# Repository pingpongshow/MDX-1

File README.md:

# MDX-1

**An open, simultaneous multi-frequency + pulse-induction metal detector — hardware, search coil and firmware.**

MDX-1 is a from-scratch detector design: a KiCad schematic and 4-layer main board, a 2-layer user-interface board, a hand-wound search coil, portable C firmware with a host simulator and test bench, and iOS/Android companion apps. The receive and transmit engine is specified around a coherent, DSP-first architecture:

- **Five simultaneous VLF frequencies** — 5.12, 10.24, 15.36, 20.48 and 40.96 kHz (harmonics 1, 2, 3, 4, 8 of a 5.12 kHz fundamental) from a single optimised 3-level look-up-table waveform, so every line falls exactly on a DFT bin and demodulates with one coherent transform.
- **Two 24-bit, 512 kSPS converters** — one digitises the receive coil, the second digitises the transmit current for exact V<sub>RX</sub>/I<sub>TX</sub> normalisation. Fixed gain, no AGC or blanking.
- **A 100 V bipolar pulse-induction mode** on the same H-bridge, plus a hybrid mode that time-interleaves PI bursts between VLF periods.
- **STM32H743** (Cortex-M7, 480 MHz) with single-crystal-coherent timing, a Bluetooth audio module, a Sharp memory LCD, GNSS find-logging and an IMU for swing-aware ground tracking.

> ### Status: experimental, design stage
> This is a **paper design that has not been built or field-tested.** The schematic is ERC-checked, the PCBs are placed and routed, the firmware core passes its host test bench, and the STM32 target layer is written against the CubeH7 HAL but has not run on hardware. Nothing here has been fabricated, assembled or measured. Component values, footprints and firmware behaviour may be wrong. **Verify everything against the primary datasheets before ordering or building.**
>
> The transmit stage switches up to **100 V** through an H-bridge into an inductive load. Treat it as a hazardous-voltage circuit: it can injure you and destroy parts if mis-built. Build and power it only if you are competent with high-voltage switching electronics.

*Main board, populated (3D view). Per-layer plots for both boards are in [`hardware/mdx1/images/`](hardware/mdx1/images/).*

## Layout

| Path | What |
|---|---|
| `hardware/mdx1/mdx1.kicad_pro` | KiCad project. Open this. |
| `hardware/mdx1/*.kicad_sch` | Root sheet + hierarchical sheets (power, tx_driver, rx_frontend, adc, mcu, ui_audio_rf, coil). |
| `hardware/mdx1/mdx1.kicad_pcb` | 135 × 92 mm 4-layer main board — footprints, nets, pours, routing, outline. |
| `hardware/mdx1/mdx1_ui.kicad_pcb` | 82 × 60 mm 2-layer UI board (LCD, keypad, pinpoint trigger, power key, LEDs, front-light). |
| `hardware/mdx1/MDX*.kicad_sym`, `MDX.pretty/` | Project-local symbol/footprint libraries. |
| `hardware/mdx1/fab/` | Fabrication packages: Gerbers, drill, assembly BOM and pick-and-place for both boards (`Gerbers/`, `BOM/`, `PNP/`); interconnect BOM; enclosure DXFs (`Case/`). |
| `hardware/mdx1/images/` | Rendered board views: per-layer plots (copper, silkscreen) and a 3D top view of each board. |
| `firmware/` | Portable core (`core/`), host physics simulator + test bench (`sim/`), STM32H743 target layer (`stm32/`). `make test` runs the bench. |
| `app/ios/` | SwiftUI companion app (BLE): live status, on-detector menu, finds map, diagnostics; built-in demo detector. |
| `app/android/` | Kotlin/Compose port of the companion app. |
| `docs/MDX-1_design_report.html` | Hardware design report. |
| `docs/MDX-1_coil_manual.html` | Search-coil build manual and off-the-shelf coil path. |
| `docs/MDX-1_firmware_guide.html` | Firmware guide with test evidence and screen renders. |
| `docs/MDX-1_assembly.md` | Board population guide (build order, critical parts, mounting). |
| `docs/MDX-1_bringup.md` | Staged first-power procedure — populate/verify one subsystem at a time. |
| `docs/MDX-1_link_protocol.md` | Phone-link protocol (frames, item table, status packet, actions). |
| `docs/MDX-1_schematic.pdf` | All schematic sheets. |
| `docs/datasheets/` | Third-party component datasheets used during the design review — **not included in this repository** (vendor copyright); part numbers are in the BOM under `hardware/mdx1/fab/`. |
| `tools/` | Design toolchain — see below. |

## The toolchain

**The KiCad schematic and boards are the source of truth — they are hand-placed and hand-routed.** The remaining tools are read-only against the boards or operate on design inputs; none of them modify the `.kicad_pcb` / `.kicad_sch` files. (The original placement/schematic generators were removed to prevent accidental overwrites of the finished layout.)

| Tool | Purpose |
|---|---|
| `tools/fab_jlc.py` | Reads the boards and writes the JLCPCB fabrication package: Gerbers + drill, assembly BOM and CPL for both boards. Does not modify the boards. |
| `tools/bom_data.json` | Maintained part database (manufacturer part numbers, packages, pricing) read by `fab_jlc.py` and `build_review.py`. |
| `tools/tx_waveform_opt.py` | Simulated-annealing optimiser for the 3-level, 5-line transmit waveform → `tx_waveform.json`. |
| `tools/coil_calc.py` | Coil electromagnetics (Neumann self/mutual inductance, null geometry, field) → `coil_calc.json`. |
| `tools/build_review.py`, `build_coil_manual.py` | Regenerate the BOM-review and coil-manual documents under `docs/`. |
| `tools/gen_fonts.py`, `pbm2png.py` | LCD bitmap fonts; simulator screen-render conversion. |

To regenerate the fabrication package after any board change (from KiCad's bundled Python):

```bash
/Applications/KiCad/KiCad.app/Contents/Frameworks/Python.framework/Versions/Current/bin/python3 tools/fab_jlc.py
```

## Firmware

```bash
cd firmware
make test        # build the portable core against the host simulator and run the test bench
make screens     # render the UI screens from the simulator
```

The core (`firmware/core/`) is target-independent C: DSP, detector logic, UI, phone link, audio. The simulator (`firmware/sim/`) provides a synthetic coil/target/ground model so the whole signal chain runs and is tested on a desktop. The STM32 layer (`firmware/stm32/`) maps the core onto the H743 peripherals.

## Before fabricating

- Run DRC to clean and re-confirm the design rules for your fab.
- Get a live distributor quote against the current BOM (part availability changes).
- Re-verify every configuration strap and value against the primary datasheets in `docs/datasheets/`.

## License

Copyright © 2026 Stephen Packer.

This project — hardware, search-coil design, firmware, apps and documentation — is licensed under the **Creative Commons Attribution-NonCommercial 4.0 International License (CC BY-NC 4.0)**. See [`LICENSE`](LICENSE) for the full text.

In short, you are free to **share and adapt** the material for **non-commercial** purposes, as long as you give appropriate credit. **Commercial use is not permitted** without separate written permission from the copyright holder.

> Note: CC licenses are not designed specifically for software. CC BY-NC 4.0 is applied here to express a single non-commercial intent across the whole project (hardware, firmware and docs together). For commercial licensing of any part, contact the author.

## Disclaimer

Provided as-is, with no warranty. This is an unbuilt, untested hobby design involving hazardous voltages. You are responsible for verifying correctness and safety before building or powering anything. Comply with the radio-emissions and other regulations in your jurisdiction before operating a transmitter of any kind.

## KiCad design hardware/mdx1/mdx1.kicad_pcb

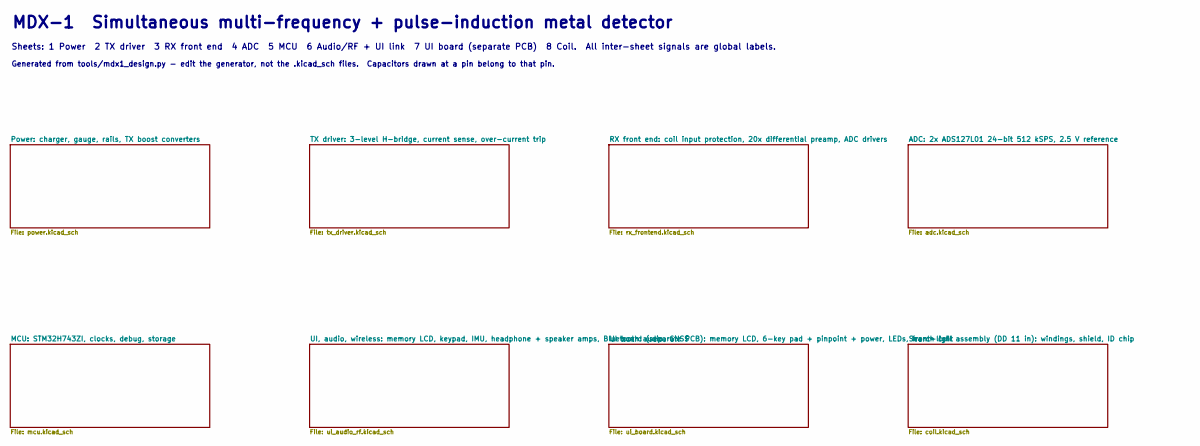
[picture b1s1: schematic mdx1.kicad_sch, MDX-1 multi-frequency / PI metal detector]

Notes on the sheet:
MDX-1 Simultaneous multi-frequency + pulse-induction metal detector
Generated from tools/mdx1_design.py - edit the generator, not the .kicad_sch files. Capacitors drawn at a pin belong to that pin.
Sheets: 1 Power 2 TX driver 3 RX front end 4 ADC 5 MCU 6 Audio/RF + UI link 7 UI board (separate PCB) 8 Coil. All inter-sheet signals are global labels.

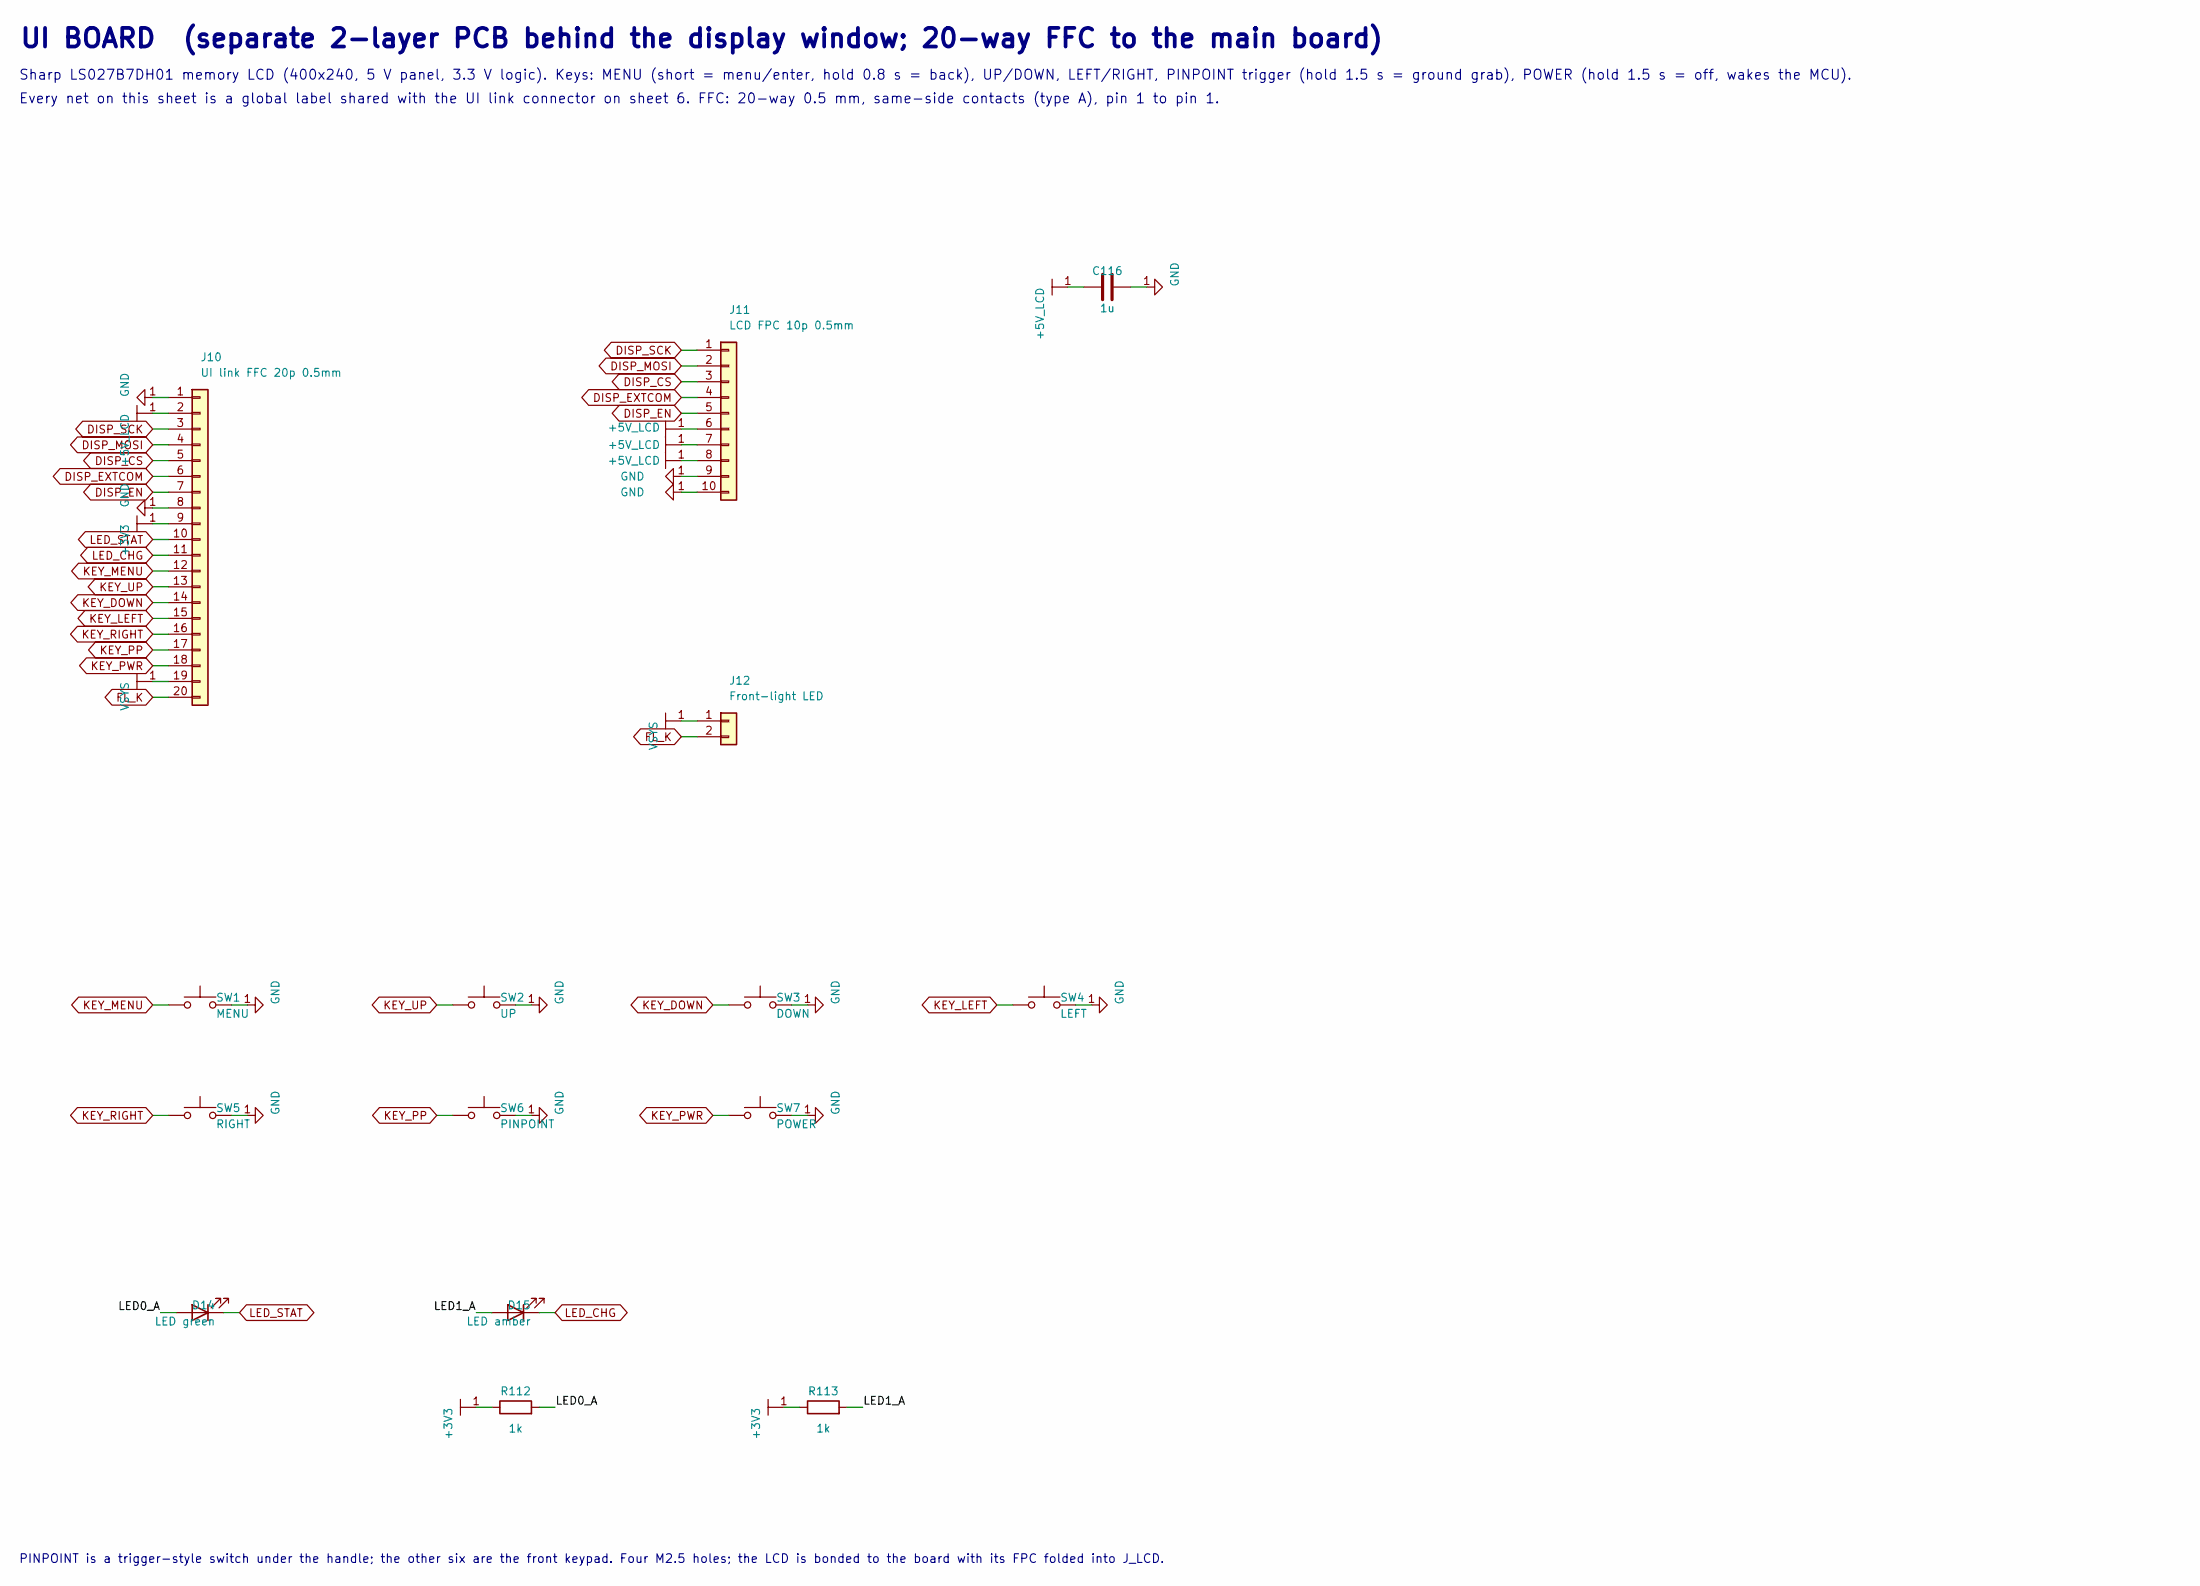
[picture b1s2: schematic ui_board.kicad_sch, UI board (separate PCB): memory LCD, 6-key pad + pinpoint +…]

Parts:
C116: 1u; C_0603_1608Metric
D14: LED green; LED_0603_1608Metric
D15: LED amber; LED_0603_1608Metric
J10: UI link FFC 20p 0.5mm; Hirose_FH12-20S-0.5SH_1x20-1MP_P0.50mm_Horizontal
J11: LCD FPC 10p 0.5mm; Hirose_FH12-10S-0.5SH_1x10-1MP_P0.50mm_Horizontal
J12: Front-light LED; JST_PH_B2B-PH-K_1x02_P2.00mm_Vertical
R112, R113: 1k; R_0402_1005Metric
SW1: MENU; SW_SPST_PTS645Sx43SMTR92
SW2: UP; SW_SPST_PTS645Sx43SMTR92
SW3: DOWN; SW_SPST_PTS645Sx43SMTR92
SW4: LEFT; SW_SPST_PTS645Sx43SMTR92
SW5: RIGHT; SW_SPST_PTS645Sx43SMTR92
SW6: PINPOINT; SW_SPST_PTS645Sx43SMTR92
SW7: POWER; SW_SPST_PTS645Sx43SMTR92

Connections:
unnamed: C116.1, J10.2, J11.6, J11.7, J11.8
unnamed: C116.2, J10.1, J10.8, J11.9, J11.10, SW1.2, SW2.2, SW3.2, SW4.2, SW5.2, SW6.2, SW7.2
unnamed: D14.1 (K), J10.10
unnamed: D14.2 (A), R112.2
unnamed: D15.1 (K), J10.11
unnamed: D15.2 (A), R113.2
unnamed: J10.3, J11.1
unnamed: J10.4, J11.2
unnamed: J10.5, J11.3
unnamed: J10.6, J11.4
unnamed: J10.7, J11.5
unnamed: J10.9, R112.1, R113.1
unnamed: J10.12, SW1.1
unnamed: J10.13, SW2.1
unnamed: J10.14, SW3.1
unnamed: J10.15, SW4.1
unnamed: J10.16, SW5.1
unnamed: J10.17, SW6.1
unnamed: J10.18, SW7.1
unnamed: J10.19, J12.1
unnamed: J10.20, J12.2

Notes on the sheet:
Sharp LS027B7DH01 memory LCD (400x240, 5 V panel, 3.3 V logic). Keys: MENU (short = menu/enter, hold 0.8 s = back), UP/DOWN, LEFT/RIGHT, PINPOINT trigger (hold 1.5 s = ground grab), POWER (hold 1.5 s = off, wakes the MCU).
PINPOINT is a trigger-style switch under the handle; the other six are the front keypad. Four M2.5 holes; the LCD is bonded to the board with its FPC folded into J_LCD.
UI BOARD (separate 2-layer PCB behind the display window; 20-way FFC to the main board)
Every net on this sheet is a global label shared with the UI link connector on sheet 6. FFC: 20-way 0.5 mm, same-side contacts (type A), pin 1 to pin 1.

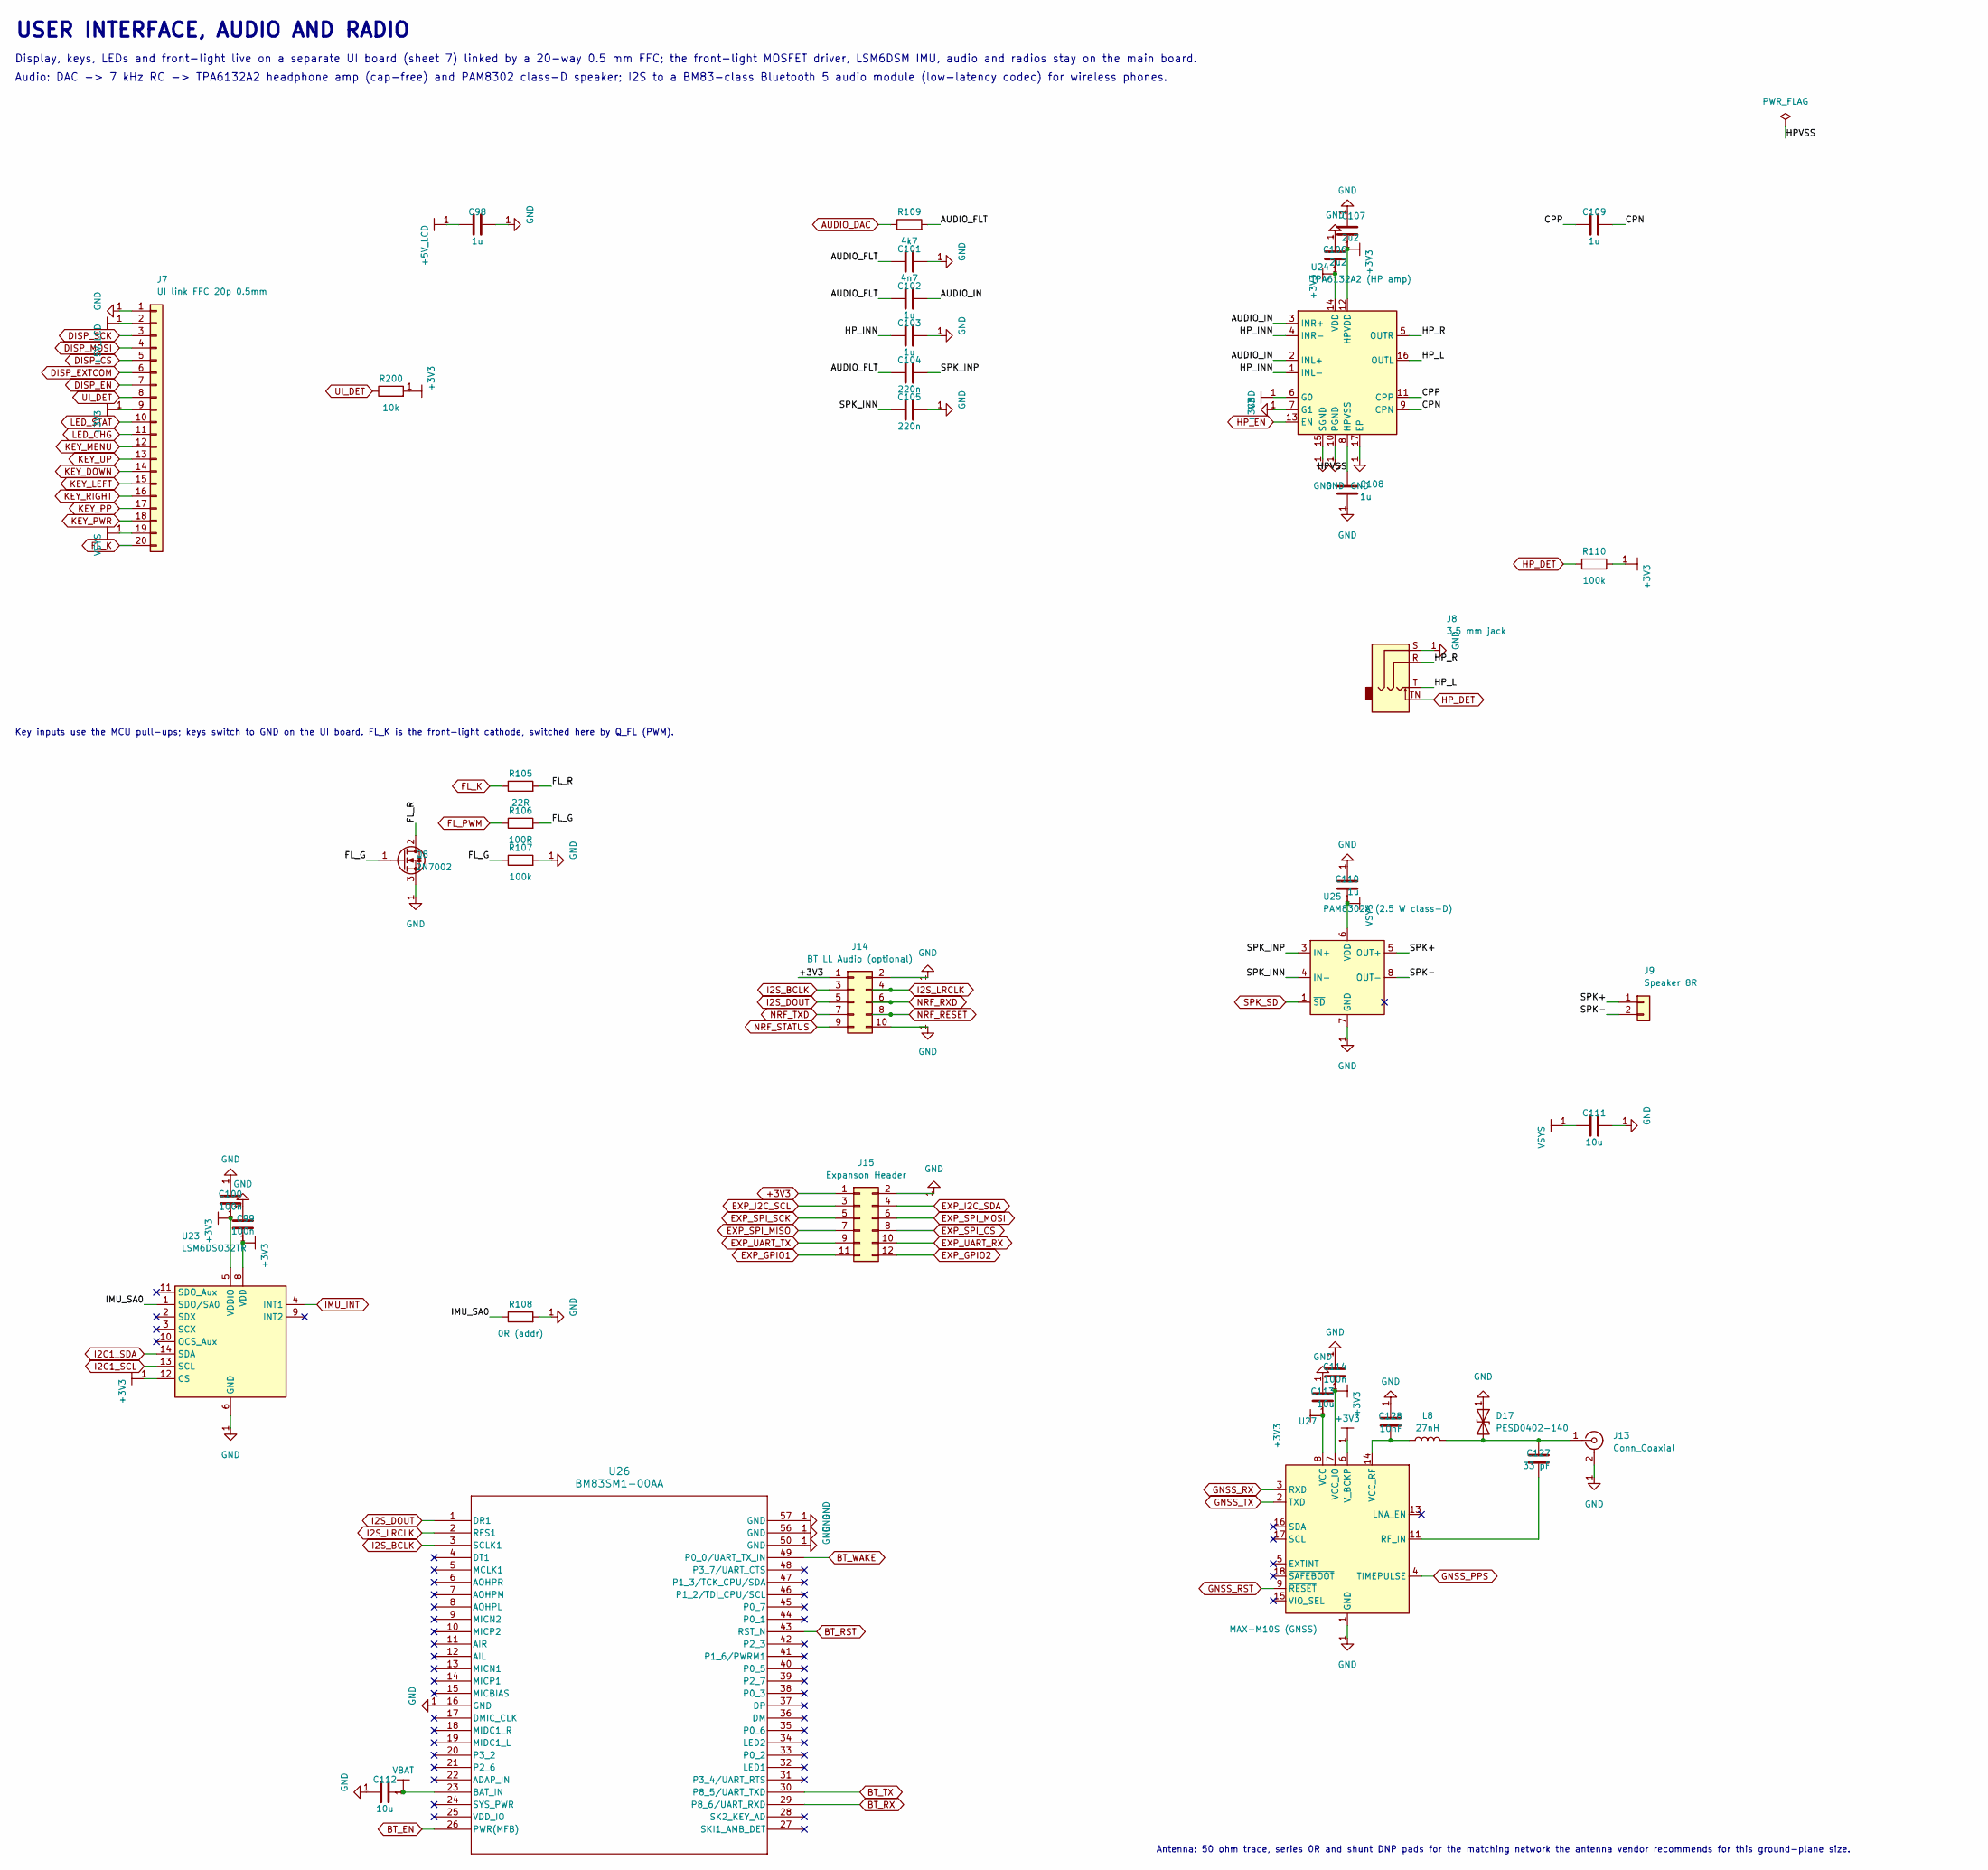
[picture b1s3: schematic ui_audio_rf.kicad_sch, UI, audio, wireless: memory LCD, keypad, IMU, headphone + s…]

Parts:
C98, C108, C109, C110: 1u; C_0603_1608Metric
C99, C100, C114: 100n; C_0402_1005Metric
C101: 4n7; C_0402_1005Metric
C102, C103: 1u; C_0402_1005Metric
C104, C105: 220n; C_0402_1005Metric
C106, C107: 2u2; C_0603_1608Metric
C111, C112, C113: 10u; C_0805_2012Metric
C127: 33 pF; C_0402_1005Metric
C128: 10nF; C_0402_1005Metric
D17: PESD0402-140; D_0402_1005Metric
J7: UI link FFC 20p 0.5mm; Hirose_FH12-20S-0.5SH_1x20-1MP_P0.50mm_Horizontal
J8: 3.5 mm jack; Jack_3.5mm_CUI_SJ-3523-SMT_Horizontal
J9: Speaker 8R; JST_PH_B2B-PH-K_1x02_P2.00mm_Vertical
J13: Conn_Coaxial; U.FL_Molex_MCRF_73412-0110_Vertical
J14: BT LL Audio (optional); Samtec_T1M-10-X-S-V_1x10-1MP_P1.0mm_Terminal_Vertical
J15: Expanson Header; Samtec_T1M-12-X-S-V_1x12-1MP_P1.0mm_Terminal_Vertical
L8: 27nH; L_0402_1005Metric
Q8: 2N7002; SOT-23
R105: 22R; R_0402_1005Metric
R106: 100R; R_0402_1005Metric
R107, R110: 100k; R_0402_1005Metric
R108: 0R (addr); R_0402_1005Metric
R109: 4k7; R_0402_1005Metric
R200: 10k; R_0402_1005Metric
U23: LSM6DSO32TR; LGA-14_3x2.5mm_P0.5mm_LayoutBorder3x4y
U24: TPA6132A2 (HP amp); Texas_RTE0016D_WQFN-16-1EP_3x3mm_P0.5mm_EP0.8x0.8mm_Thermal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
U25: PAM8302A (2.5 W class-D); MSOP-8-1EP_3x3mm_P0.65mm_EP1.68x1.88mm
U26: BM83SM1-00AA; BM83_MCH
U27: MAX-M10S (GNSS); ublox_MAX

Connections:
+3V3: C99.1, C100.1, C106.1, C107.1, C113.1, C114.1, J7.9, J14.1, J15.1, R110.2, R200.2, U23.5 (VDDIO), U23.8 (VDD), U23.12 (CS), U24.6 (G0), U24.12 (HPVDD), U24.14 (VDD), U27.6 (V_BCKP), U27.7 (VCC_IO), U27.8 (VCC); also elsewhere on the board
+5V_LCD: C98.1, J7.2; also elsewhere on the board
/UI, audio, wireless: memory LCD, keypad, IMU, headphone + speaker amps, Blueto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: C101.1, C102.1, C104.1, R109.2
/UI, audio, wireless: memory LCD, keypad, IMU, headphone + speaker amps, Blueto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: C102.2, U24.2 (INL+), U24.3 (INR+)
/UI, audio, wireless: memory LCD, keypad, IMU, headphone + speaker amps, Blueto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: C109.2, U24.9 (CPN)
/UI, audio, wireless: memory LCD, keypad, IMU, headphone + speaker amps, Blueto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: C109.1, U24.11 (CPP)
/UI, audio, wireless: memory LCD, keypad, IMU, headphone + speaker amps, Blueto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: Q8.1 (G), R106.2, R107.1
/UI, audio, wireless: memory LCD, keypad, IMU, headphone + speaker amps, Blueto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: Q8.2 (D), R105.2
/UI, audio, wireless: memory LCD, keypad, IMU, headphone + speaker amps, Blueto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: C108.1, U24.8 (HPVSS)
/UI, audio, wireless: memory LCD, keypad, IMU, headphone + speaker amps, Blueto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: C103.1, U24.1 (INL-), U24.4 (INR-)
/UI, audio, wireless: memory LCD, keypad, IMU, headphone + speaker amps, Blueto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: J8.T, U24.16 (OUTL)
/UI, audio, wireless: memory LCD, keypad, IMU, headphone + speaker amps, Blueto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: J8.R, U24.5 (OUTR)
/UI, audio, wireless: memory LCD, keypad, IMU, headphone + speaker amps, Blueto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: R108.1, U23.1 (SDO/SA0)
/UI, audio, wireless: memory LCD, keypad, IMU, headphone + speaker amps, Blueto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: J9.1, U25.5 (OUT+)
/UI, audio, wireless: memory LCD, keypad, IMU, headphone + speaker amps, Blueto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: J9.2, U25.8 (OUT-)
/UI, audio, wireless: memory LCD, keypad, IMU, headphone + speaker amps, Blueto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: C105.1, U25.4 (IN-)
/UI, audio, wireless: memory LCD, keypad, IMU, headphone + speaker amps, Blueto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: C104.2, U25.3 (IN+)
AUDIO_DAC: R109.1; also elsewhere on the board
BT_EN: U26.26 (PWR(MFB)); also elsewhere on the board
BT_RST: U26.43 (RST_N); also elsewhere on the board
BT_RX: U26.29 (P8_6/UART_RXD); also elsewhere on the board
BT_TX: U26.30 (P8_5/UART_TXD); also elsewhere on the board
BT_WAKE: U26.49 (P0_0/UART_TX_IN); also elsewhere on the board
DISP_CS: J7.5; also elsewhere on the board
DISP_EN: J7.7; also elsewhere on the board
DISP_EXTCOM: J7.6; also elsewhere on the board
DISP_MOSI: J7.4; also elsewhere on the board
DISP_SCK: J7.3; also elsewhere on the board
EXP_GPIO1: J15.11; also elsewhere on the board
EXP_GPIO2: J15.12; also elsewhere on the board
EXP_I2C_SCL: J15.3; also elsewhere on the board
EXP_I2C_SDA: J15.4; also elsewhere on the board
EXP_SPI_CS: J15.8; also elsewhere on the board
EXP_SPI_MISO: J15.7; also elsewhere on the board
EXP_SPI_MOSI: J15.6; also elsewhere on the board
EXP_SPI_SCK: J15.5; also elsewhere on the board
EXP_UART_RX: J15.10; also elsewhere on the board
EXP_UART_TX: J15.9; also elsewhere on the board
FL_K: J7.20, R105.1
FL_PWM: R106.1; also elsewhere on the board
GNSS_PPS: U27.4 (TIMEPULSE); also elsewhere on the board
GNSS_RST: U27.9 (~RESET); also elsewhere on the board
GNSS_RX: U27.3 (RXD); also elsewhere on the board
GNSS_TX: U27.2 (TXD); also elsewhere on the board
HP_DET: J8.TN, R110.1; also elsewhere on the board
HP_EN: U24.13 (EN); also elsewhere on the board
I2C1_SCL: U23.13 (SCL); also elsewhere on the board
I2C1_SDA: U23.14 (SDA); also elsewhere on the board
I2S_BCLK: J14.3, U26.3 (SCLK1); also elsewhere on the board
I2S_DOUT: J14.5, U26.1 (DR1); also elsewhere on the board
I2S_LRCLK: J14.4, U26.2 (RFS1); also elsewhere on the board
IMU_INT: U23.4 (INT1); also elsewhere on the board
KEY_DOWN: J7.14; also elsewhere on the board
KEY_LEFT: J7.15; also elsewhere on the board
KEY_MENU: J7.12; also elsewhere on the board
KEY_PP: J7.17; also elsewhere on the board
KEY_PWR: J7.18; also elsewhere on the board
KEY_RIGHT: J7.16; also elsewhere on the board
KEY_UP: J7.13; also elsewhere on the board
LED_CHG: J7.11; also elsewhere on the board
LED_STAT: J7.10; also elsewhere on the board
NRF_RESET: J14.8; also elsewhere on the board
NRF_RXD: J14.6; also elsewhere on the board
NRF_STATUS: J14.9; also elsewhere on the board
NRF_TXD: J14.7; also elsewhere on the board
unnamed: C127.2, D17.2 (A2), J13.1 (In), L8.2
unnamed: C127.1, U27.11 (RF_IN)
unnamed: C128.1, L8.1, U27.14 (VCC_RF)
SPK_SD: U25.1 (~SD); also elsewhere on the board
UI_DET: J7.8, R200.1; also elsewhere on the board
VBAT: C112.1, U26.23 (BAT_IN); also elsewhere on the board
VSYS: C110.1, C111.1, J7.19, U25.6 (VDD); also elsewhere on the board

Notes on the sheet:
Display, keys, LEDs and front-light live on a separate UI board (sheet 7) linked by a 20-way 0.5 mm FFC; the front-light MOSFET driver, LSM6DSM IMU, audio and radios stay on the main board.
Antenna: 50 ohm trace, series 0R and shunt DNP pads for the matching network the antenna vendor recommends for this ground-plane size.
Key inputs use the MCU pull-ups; keys switch to GND on the UI board. FL_K is the front-light cathode, switched here by Q_FL (PWM).
USER INTERFACE, AUDIO AND RADIO
Audio: DAC -> 7 kHz RC -> TPA6132A2 headphone amp (cap-free) and PAM8302 class-D speaker; I2S to a BM83-class Bluetooth 5 audio module (low-latency codec) for wireless phones.
